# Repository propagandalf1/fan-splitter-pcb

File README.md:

# Fan-Splitter-PCB
A PCB designed to connect multiple 4 pin PWM fans without cable splitters.

## current

* ordered prototype -> corrected a mistake
* added 2 way version
* added Mora Version

## To Do

* ~~confirm working prototype~~ / ordering new prototypes
* adding 4 way splitter
* doing some good renders :D

## Version 0.2

I added 2 more connectors so now the splitter supports 140 AND 120mm fans within a single pcb. So you only have to order one batch to connect a 420 and a 360 radiator instead of ordering 2 seperate batches and different pcbs as intended in the first place.

## Version 0.1

Currently it only supports 360 radiators or 3x120mm fan configurations.
More will come in the future. Also feel free to adopt this idea to your own needs.

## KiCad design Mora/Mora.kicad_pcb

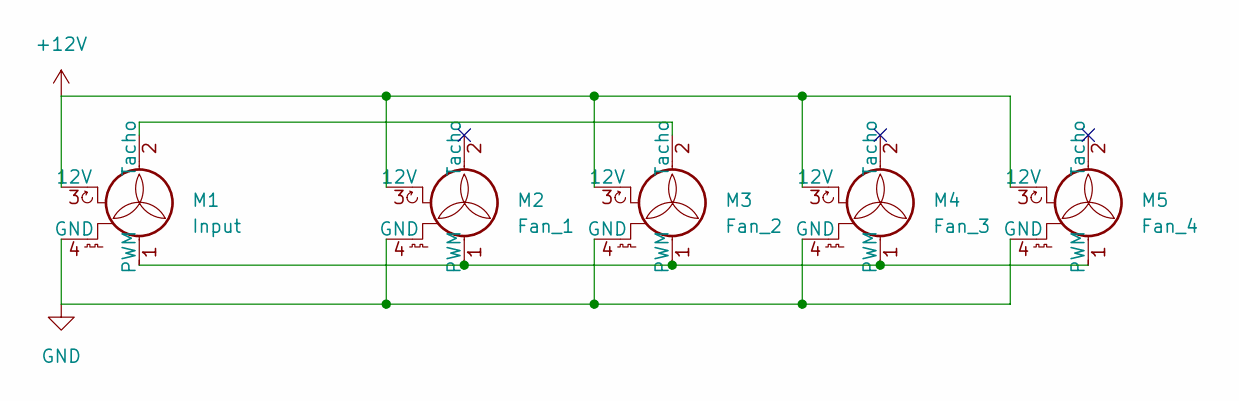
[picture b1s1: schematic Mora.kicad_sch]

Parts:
M1: Input; PinHeader_1x04_P2.54mm_Horizontal
M2: Fan_1; PinHeader_1x04_P2.54mm_Horizontal
M3: Fan_2; PinHeader_1x04_P2.54mm_Horizontal
M4: Fan_3; PinHeader_1x04_P2.54mm_Horizontal
M5: Fan_4; PinHeader_1x04_P2.54mm_Horizontal

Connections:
+12V: M1.3 (12V), M2.3 (12V), M3.3 (12V), M4.3 (12V), M5.3 (12V)
GND: M1.4 (GND), M2.4 (GND), M3.4 (GND), M4.4 (GND), M5.4 (GND)
unnamed: M1.1 (PWM), M2.1 (PWM), M3.1 (PWM), M4.1 (PWM), M5.1 (PWM)
unnamed: M1.2 (Tacho), M3.2 (Tacho)

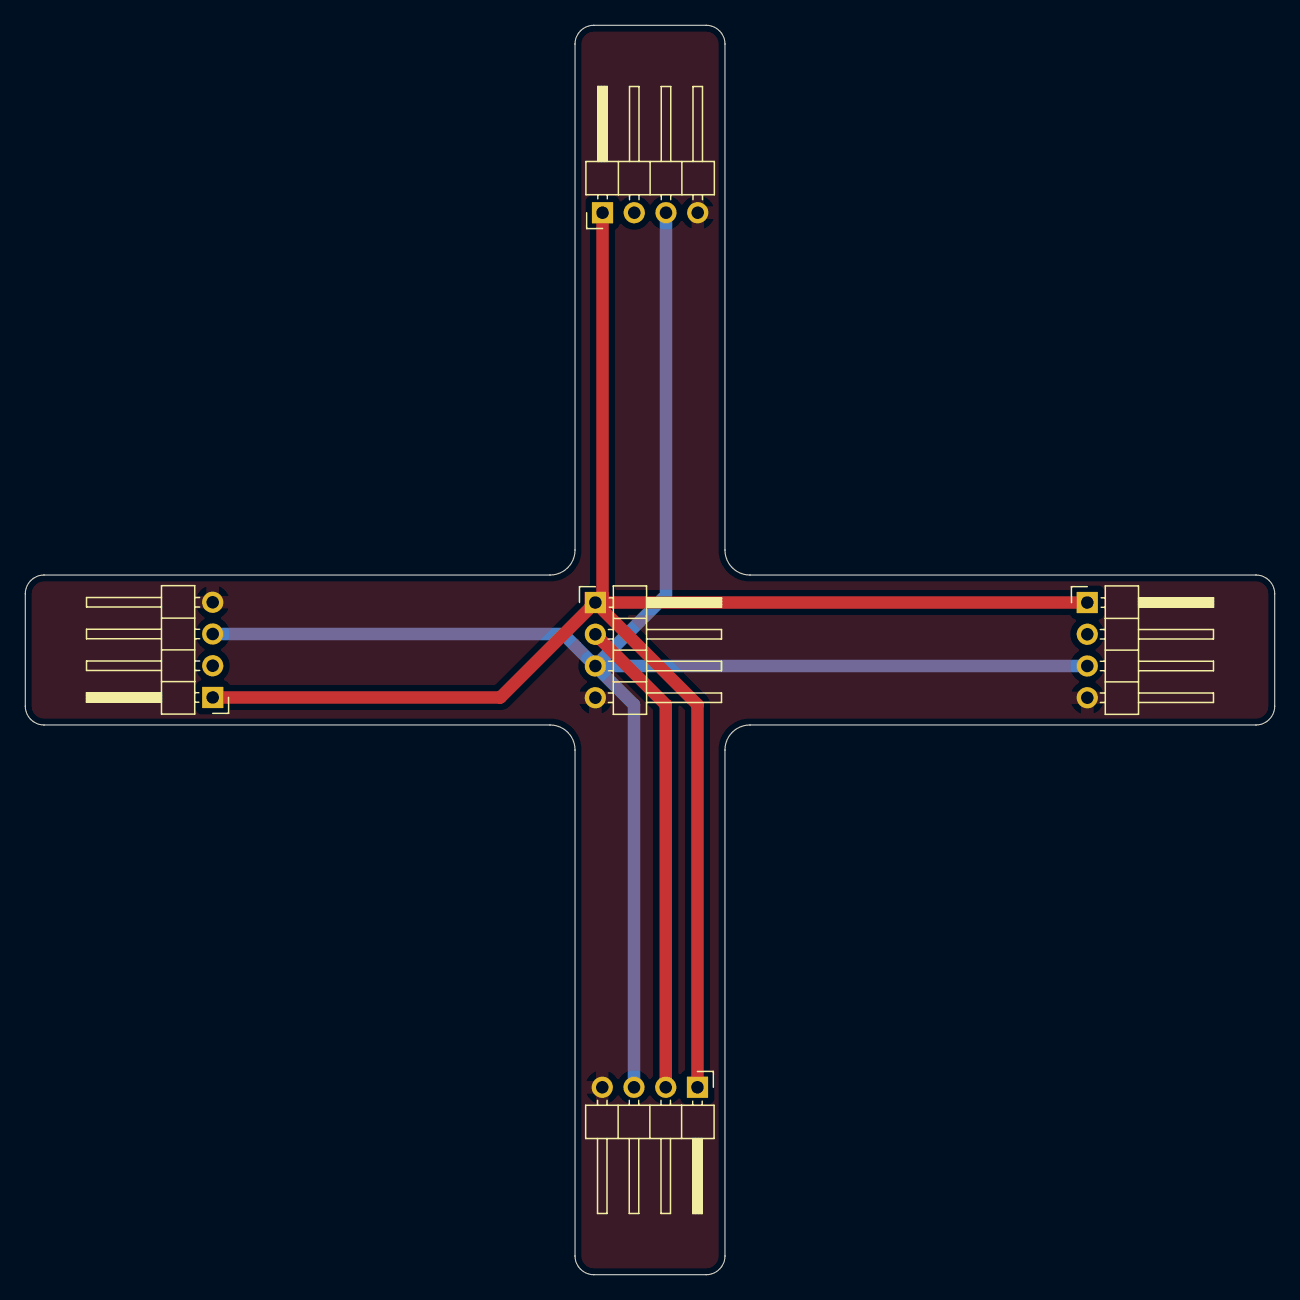
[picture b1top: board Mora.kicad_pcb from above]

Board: 2 copper layers, 100.0 x 100.0 mm, 5 parts (0 on the bottom side), 4 nets.

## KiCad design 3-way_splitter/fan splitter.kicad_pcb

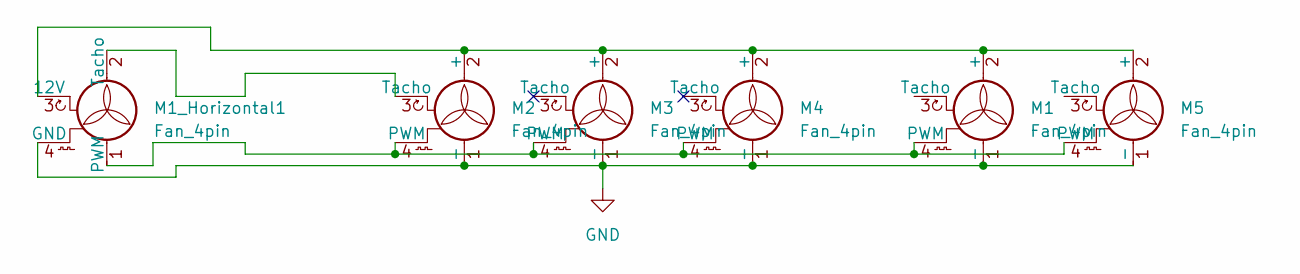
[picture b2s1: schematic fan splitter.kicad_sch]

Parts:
M1, M2, M3, M4, M5: Fan_4pin; PinHeader_1x04_P2.54mm_Vertical
M1_Horizontal1: Fan_4pin; PinHeader_1x04_P2.54mm_Horizontal

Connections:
GND: M1.1 (-), M1_Horizontal1.4 (GND), M2.1 (-), M3.1 (-), M4.1 (-), M5.1 (-)
unnamed: M1.4 (PWM), M1_Horizontal1.1 (PWM), M2.4 (PWM), M3.4 (PWM), M4.4 (PWM), M5.4 (PWM)
unnamed: M1_Horizontal1.2 (Tacho), M2.3 (Tacho)
unnamed: M1.2 (+), M1_Horizontal1.3 (12V), M2.2 (+), M3.2 (+), M4.2 (+), M5.2 (+)

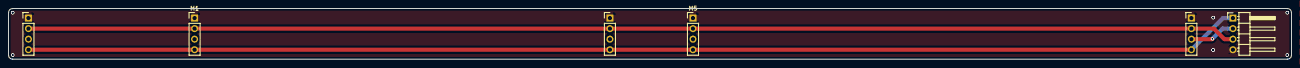
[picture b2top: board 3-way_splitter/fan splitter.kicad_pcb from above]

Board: 2 copper layers, 308.9 x 12.2 mm, 6 parts (0 on the bottom side), 4 nets.

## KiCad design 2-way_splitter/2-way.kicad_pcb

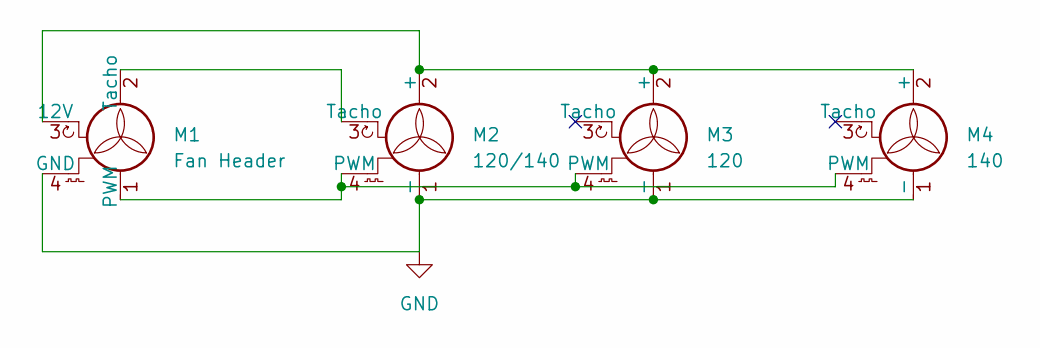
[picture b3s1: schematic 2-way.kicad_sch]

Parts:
M1: Fan Header; PinHeader_1x04_P2.54mm_Horizontal
M2: 120/140; PinHeader_1x04_P2.54mm_Vertical
M3: 120; PinHeader_1x04_P2.54mm_Vertical
M4: 140; PinHeader_1x04_P2.54mm_Vertical

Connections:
GND: M1.4 (GND), M2.1 (-), M3.1 (-), M4.1 (-)
unnamed: M1.1 (PWM), M2.4 (PWM), M3.4 (PWM), M4.4 (PWM)
unnamed: M1.2 (Tacho), M2.3 (Tacho)
unnamed: M1.3 (12V), M2.2 (+), M3.2 (+), M4.2 (+)

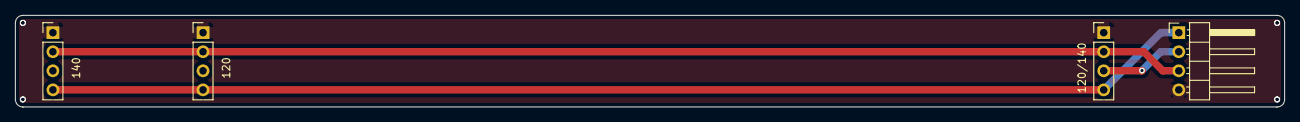
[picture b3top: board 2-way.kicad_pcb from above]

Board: 2 copper layers, 169.1 x 12.2 mm, 4 parts (0 on the bottom side), 4 nets.

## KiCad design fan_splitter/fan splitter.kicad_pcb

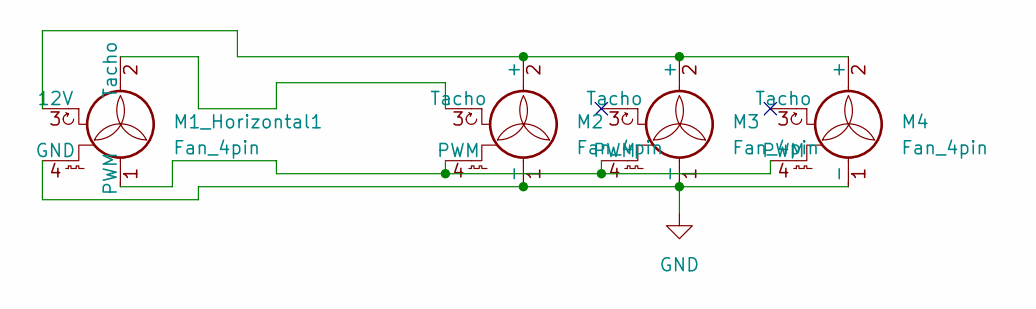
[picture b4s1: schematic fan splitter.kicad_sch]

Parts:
M1_Horizontal1: Fan_4pin; PinHeader_1x04_P2.54mm_Horizontal
M2, M3, M4: Fan_4pin; PinHeader_1x04_P2.54mm_Vertical

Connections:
GND: M1_Horizontal1.4 (GND), M2.1 (-), M3.1 (-), M4.1 (-)
unnamed: M1_Horizontal1.3 (12V), M2.2 (+), M3.2 (+), M4.2 (+)
unnamed: M1_Horizontal1.2 (Tacho), M2.3 (Tacho)
unnamed: M1_Horizontal1.1 (PWM), M2.4 (PWM), M3.4 (PWM), M4.4 (PWM)

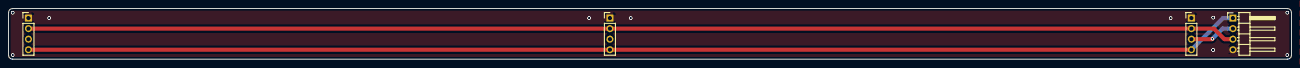
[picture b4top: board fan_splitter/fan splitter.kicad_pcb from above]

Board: 2 copper layers, 308.9 x 12.2 mm, 4 parts (0 on the bottom side), 4 nets.
